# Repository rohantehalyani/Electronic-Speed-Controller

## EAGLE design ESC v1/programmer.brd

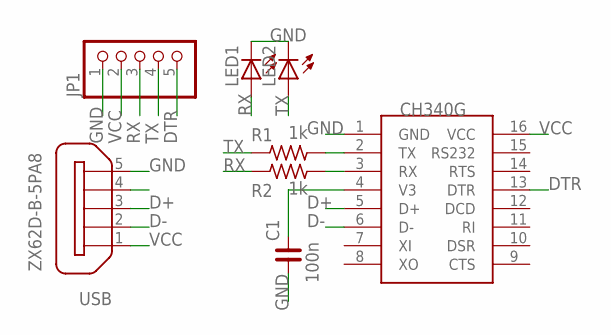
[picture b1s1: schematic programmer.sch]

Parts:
C1: 100n; C2012
JP1: PINHD-1X5; 1X05
LED1, LED2: LEDCHIP-LED0805; CHIP-LED0805
R1, R2: 1k; R2012
U$1: CH340G; SOIC16
USB: ZX62D-B-5PA8

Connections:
D+: U$1.5 (D+), USB.3
D-: U$1.6 (D-), USB.2
DTR: JP1.5, U$1.13 (DTR)
GND: C1.1, JP1.1, LED1.C, LED2.C, U$1.1 (GND), USB.5
unnamed: C1.2, U$1.4 (V3)
unnamed: R1.2, U$1.2 (TX)
unnamed: R2.2, U$1.3 (RX)
RX: JP1.3, LED1.A, R2.1
TX: JP1.4, LED2.A, R1.1
VCC: JP1.2, U$1.16 (VCC), USB.1

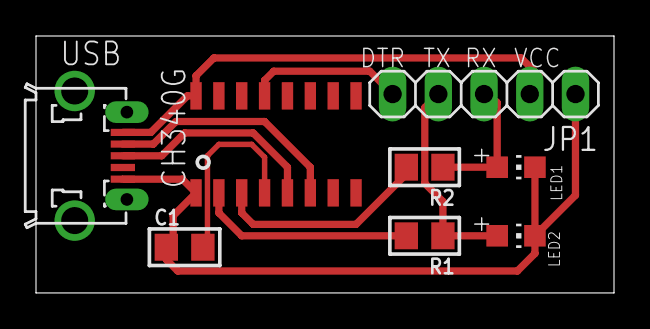
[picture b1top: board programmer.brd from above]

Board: 2 copper layers, 32.1 x 14.3 mm, 8 parts (0 on the bottom side), 10 nets.

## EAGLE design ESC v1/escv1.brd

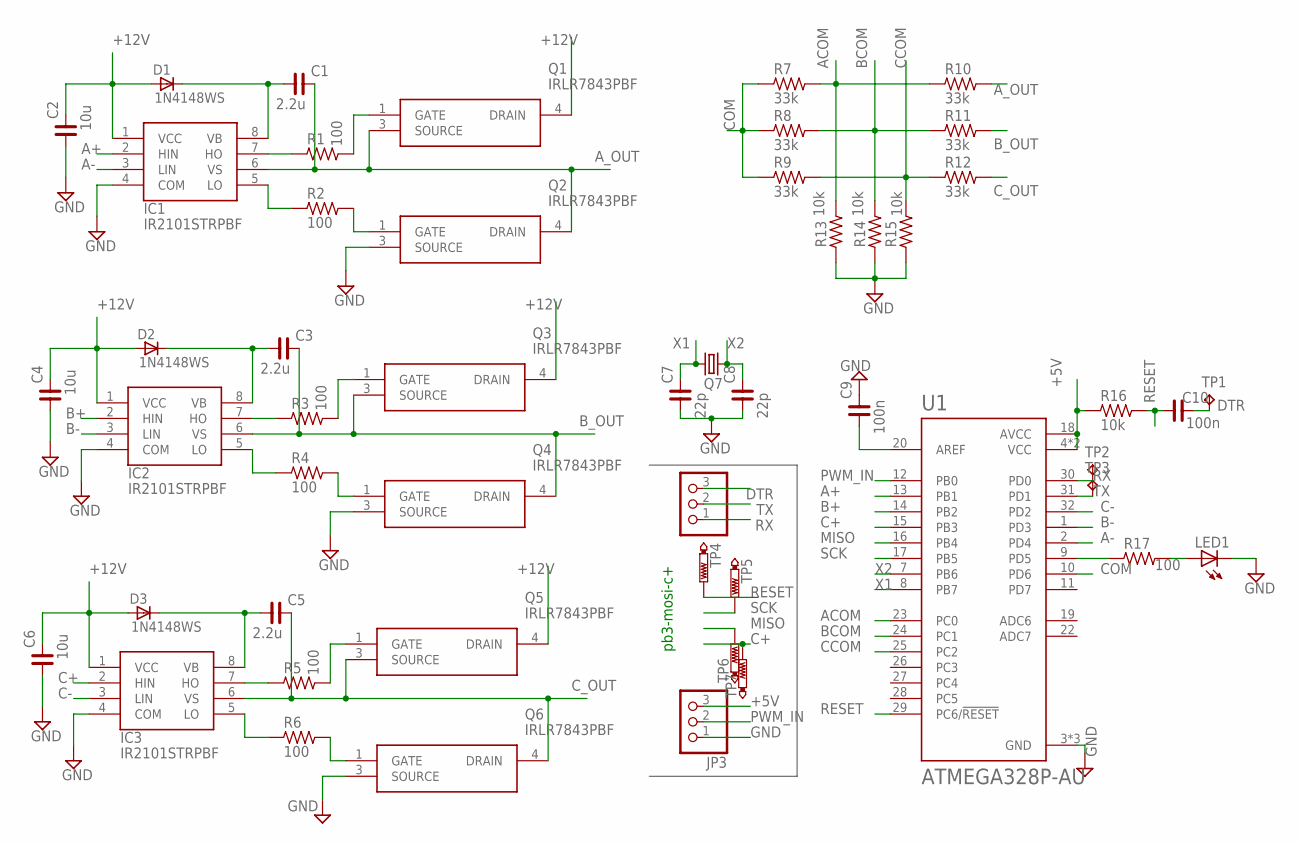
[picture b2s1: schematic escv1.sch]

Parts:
C1, C3, C5: 2.2u; C2012
C2, C4, C6: 10u; C2012
C7, C8: 22p; C2012
C9, C10: 100n; C2012
D1, D2, D3: 1N4148WS; SOD323F
IC1, IC2, IC3: IR2101STRPBF; SOIC127P600X175-8N
JP1, JP3: PINHD-1X3; 1X03
LED1: LEDCHIP-LED0805; CHIP-LED0805
Q1, Q2, Q3, Q4, Q5, Q6: IRLR7843PBF; D-PAK(TO-252AA)_1
Q7: CRYSTALSM49; SM49
R1, R2, R3, R4, R5, R6, R17: 100; R2012
R7, R8, R9, R10, R11, R12: 33k; R2012
R13, R14, R15, R16: 10k; R2012
TP1, TP2, TP3: TPTP07R; TP07R
TP4, TP5, TP6, TP7: PTR1TP10R; TP10R
U1: ATMEGA328P-AU; QFP80P900X900X120-32N

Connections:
+5V: JP3.3, R16.1, U1.4 (VCC), U1.6 (VCC), U1.18 (AVCC)
+12V: C2.2, C4.2, C6.2, D1.A, D2.A, D3.A, IC1.1 (VCC), IC2.1 (VCC), IC3.1 (VCC), Q1.4 (DRAIN), Q3.4 (DRAIN), Q5.4 (DRAIN)
A+: IC1.2 (HIN), U1.13 (PB1)
A-: IC1.3 (LIN), U1.2 (PD4)
ACOM: R7.2, R10.1, R13.2, U1.23 (PC0)
A_OUT: C1.2, IC1.6 (VS), Q1.3 (SOURCE), Q2.4 (DRAIN), R10.2
B+: IC2.2 (HIN), U1.14 (PB2)
B-: IC2.3 (LIN), U1.1 (PD3)
BCOM: R8.2, R11.1, R14.2, U1.24 (PC1)
B_OUT: C3.2, IC2.6 (VS), Q3.3 (SOURCE), Q4.4 (DRAIN), R11.2
C+: IC3.2 (HIN), TP7.TP, U1.15 (PB3)
C-: IC3.3 (LIN), U1.32 (PD2)
CCOM: R9.2, R12.1, R15.2, U1.25 (PC2)
COM: R7.1, R8.1, R9.1, U1.10 (PD6)
C_OUT: C5.2, IC3.6 (VS), Q5.3 (SOURCE), Q6.4 (DRAIN), R12.2
DTR: C10.2, JP1.3, TP1.TP
GND: C2.1, C4.1, C6.1, C7.1, C8.1, C9.2, IC1.4 (COM), IC2.4 (COM), IC3.4 (COM), JP3.1, LED1.C, Q2.3 (SOURCE), Q4.3 (SOURCE), Q6.3 (SOURCE), R13.1, R14.1, R15.1, U1.3 (GND), U1.5 (GND), U1.21 (GND)
MISO: TP6.TP, U1.16 (PB4)
unnamed: C3.1, D2.C, IC2.8 (VB)
unnamed: C1.1, D1.C, IC1.8 (VB)
unnamed: IC1.7 (HO), R1.1
unnamed: IC1.5 (LO), R2.1
unnamed: Q1.1 (GATE), R1.2
unnamed: Q2.1 (GATE), R2.2
unnamed: IC2.7 (HO), R3.1
unnamed: IC2.5 (LO), R4.1
unnamed: Q3.1 (GATE), R3.2
unnamed: Q4.1 (GATE), R4.2
unnamed: C5.1, D3.C, IC3.8 (VB)
unnamed: IC3.7 (HO), R5.1
unnamed: IC3.5 (LO), R6.1
unnamed: Q5.1 (GATE), R5.2
unnamed: Q6.1 (GATE), R6.2
unnamed: C9.1, U1.20 (AREF)
unnamed: R17.1, U1.9 (PD5)
unnamed: LED1.A, R17.2
PWM_IN: JP3.2, U1.12 (PB0)
RESET: C10.1, R16.2, TP4.TP, U1.29 (PC6/!RESET)
RX: JP1.1, TP2.TP, U1.30 (PD0)
SCK: TP5.TP, U1.17 (PB5)
TX: JP1.2, TP3.TP, U1.31 (PD1)
X1: C7.2, Q7.1, U1.8 (PB7)
X2: C8.2, Q7.2, U1.7 (PB6)

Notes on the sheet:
pb3-mosi-c+

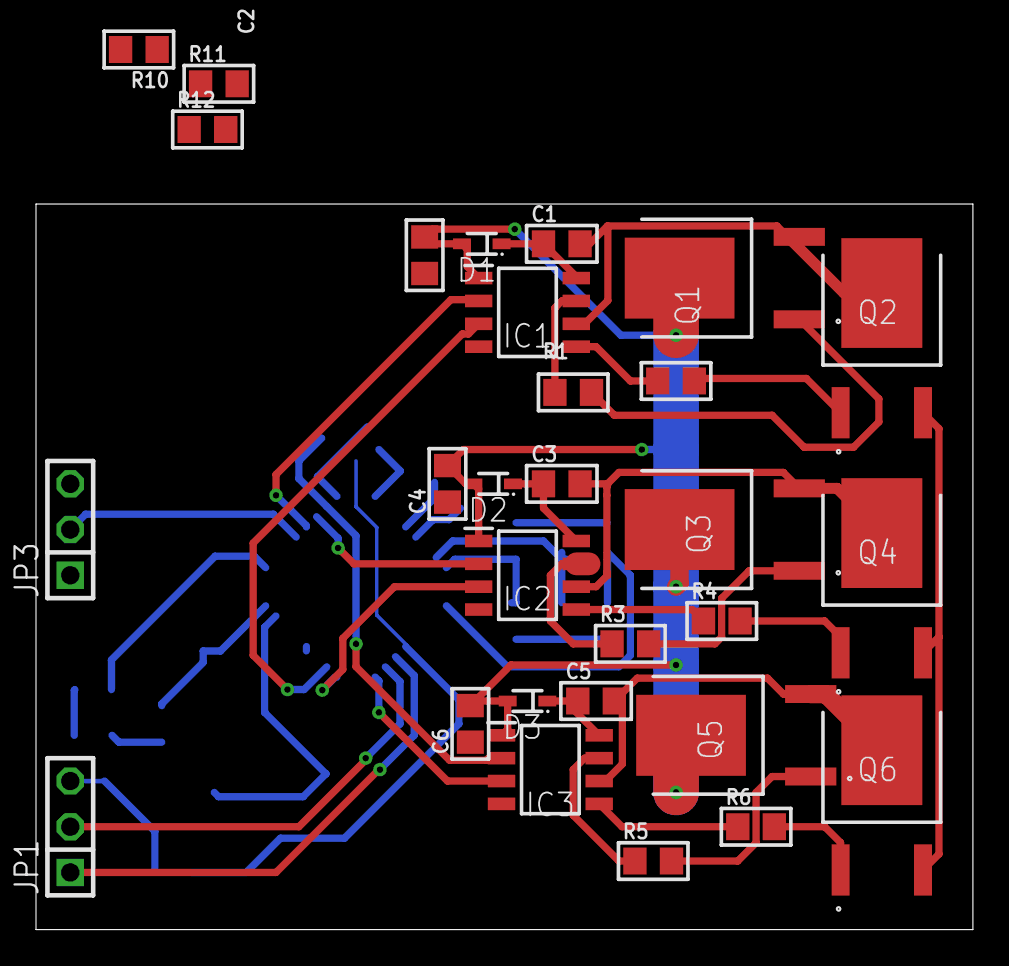
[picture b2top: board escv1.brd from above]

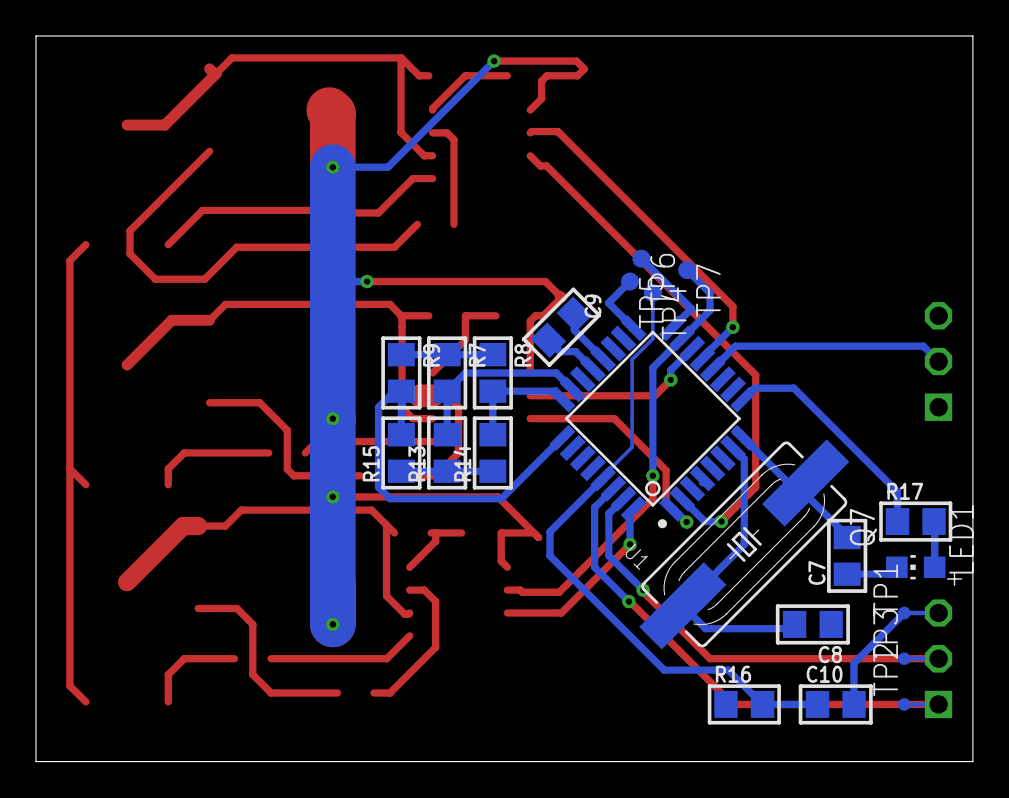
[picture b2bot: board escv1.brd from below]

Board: 2 copper layers, 52.0 x 40.3 mm, 51 parts (22 on the bottom side), 43 nets.

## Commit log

2020-07-23 version 1

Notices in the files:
parts and their libraries:
rc-master-smd: Copyright (C) 2007, Bob Starr
